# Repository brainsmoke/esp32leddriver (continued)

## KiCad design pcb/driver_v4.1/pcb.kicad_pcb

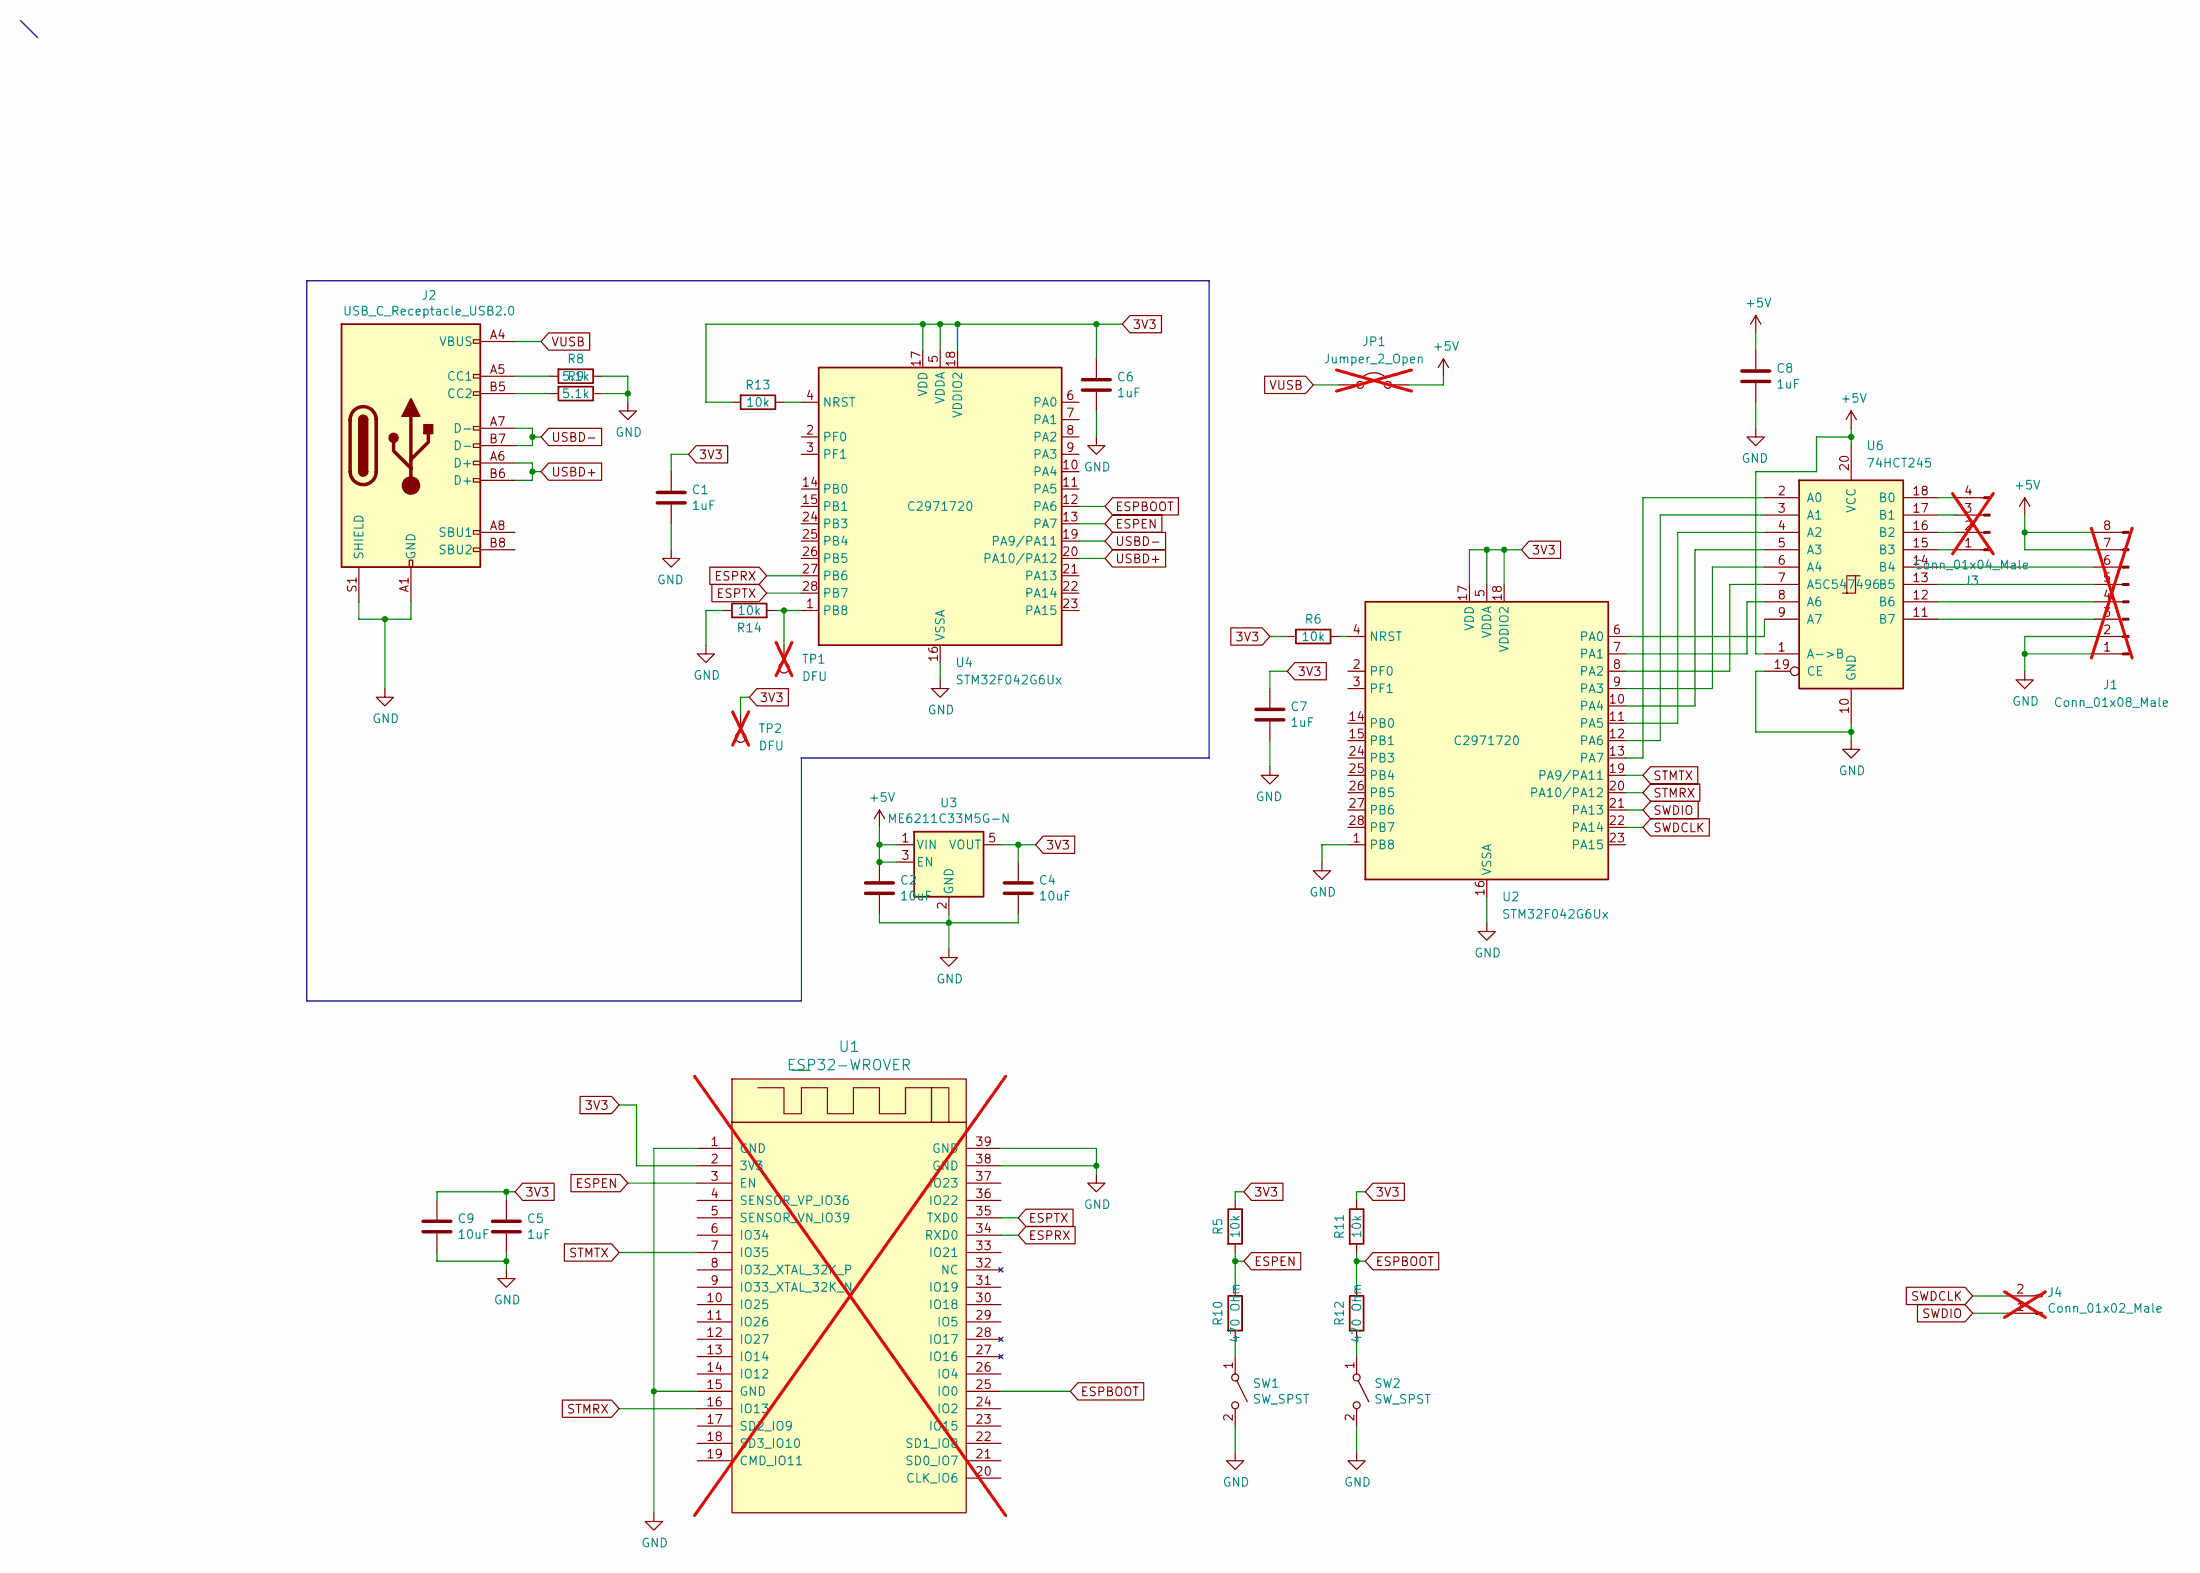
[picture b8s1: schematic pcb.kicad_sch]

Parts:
C1, C5, C6, C7, C8: 1uF; C_0402_1005Metric; LCSC C52923
C2, C4, C9: 10uF; C_0603_1608Metric; LCSC C19702
J1: Conn_01x08_Male; PinHeader_1x08_P2.54mm_Vertical; not fitted
J2: USB_C_Receptacle_USB2.0; USB_C_Receptacle_HRO_TYPE-C-31-M-12; LCSC C165948
J3: Conn_01x04_Male; PinHeader_1x04_P2.54mm_Vertical; not fitted
J4: Conn_01x02_Male; PinHeader_1x02_P2.54mm_Vertical; not fitted
JP1: Jumper_2_Open; R_0805_2012Metric; not fitted
R5, R6, R11, R13, R14: 10k; R_0402_1005Metric; LCSC C25744
R8, R9: 5.1k; R_0402_1005Metric; LCSC C25905
R10, R12: 470 Ohm; R_0402_1005Metric; LCSC C25117
SW1, SW2: SW_SPST; SW_Push_1P1T_NO_CK_KMR2; LCSC C318893
TP1, TP2: DFU; TestPoint_Pad_D1.0mm; not fitted
U1: ESP32-WROVER; XCVR_ESP32-WROVER; not fitted
U2, U4: STM32F042G6Ux; QFN-28_4x4mm_P0.5mm; LCSC C2971720
U3: ME6211C33M5G-N; SOT-23-5; LCSC C82942
U6: 74HCT245; DHVQFN-20-1EP_2.5x4.5mm_P0.5mm_EP1x3mm; LCSC C547496

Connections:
3V3: C1.1, C4.1, C5.1, C6.1, C7.1, C9.1, R5.1, R6.2, R11.1, R13.2, TP2.1, U1.2 (3V3), U2.5 (VDDA), U2.17 (VDD), U2.18 (VDDIO2), U3.5 (VOUT), U4.5 (VDDA), U4.17 (VDD), U4.18 (VDDIO2)
+5V: C2.1, C8.1, J1.7, J1.8, JP1.2 (B), U3.1 (VIN), U3.3 (EN), U6.1 (A->B), U6.20 (VCC)
ESPBOOT: R11.2, R12.1, U1.25 (IO0), U4.12 (PA6)
ESPEN: R5.2, R10.1, U1.3 (EN), U4.13 (PA7)
ESPRX: U1.34 (RXD0), U4.27 (PB6)
ESPTX: U1.35 (TXD0), U4.28 (PB7)
GND: C1.2, C2.2, C4.2, C5.2, C6.2, C7.2, C8.2, C9.2, J1.1, J1.2, J2.A1 (GND), J2.A12 (GND), J2.B1 (GND), J2.B12 (GND), J2.S1 (SHIELD), R8.1, R9.1, R14.1, SW1.2 (B), SW2.2 (B), U1.1 (GND), U1.15 (GND), U1.38 (GND), U1.39 (GND), U2.1 (PB8), U2.16 (VSSA), U3.2 (GND), U4.16 (VSSA), U6.10 (GND), U6.19 (CE)
unnamed: J1.3, U6.11 (B7)
unnamed: J1.4, U6.12 (B6)
unnamed: J1.5, U6.13 (B5)
unnamed: J1.6, U6.14 (B4)
unnamed: J2.A5 (CC1), R8.2
unnamed: J2.B5 (CC2), R9.2
unnamed: J3.1, U6.15 (B3)
unnamed: J3.2, U6.16 (B2)
unnamed: J3.3, U6.17 (B1)
unnamed: J3.4, U6.18 (B0)
unnamed: R10.2, SW1.1 (A)
unnamed: R12.2, SW2.1 (A)
unnamed: R6.1, U2.4 (NRST)
unnamed: U2.6 (PA0), U6.9 (A7)
unnamed: U2.7 (PA1), U6.8 (A6)
unnamed: U2.8 (PA2), U6.7 (A5)
unnamed: U2.9 (PA3), U6.6 (A4)
unnamed: U2.10 (PA4), U6.5 (A3)
unnamed: U2.11 (PA5), U6.4 (A2)
unnamed: U2.12 (PA6), U6.3 (A1)
unnamed: U2.13 (PA7), U6.2 (A0)
unnamed: R13.1, U4.4 (NRST)
unnamed: R14.2, TP1.1, U4.1 (PB8)
STMRX: U1.16 (IO13), U2.20 (PA10/PA12)
STMTX: U1.7 (IO35), U2.19 (PA9/PA11)
SWDCLK: J4.2, U2.22 (PA14)
SWDIO: J4.1, U2.21 (PA13)
USBD+: J2.A6 (D+), J2.B6 (D+), U4.20 (PA10/PA12)
USBD-: J2.A7 (D-), J2.B7 (D-), U4.19 (PA9/PA11)
VUSB: J2.A4 (VBUS), J2.A9 (VBUS), J2.B4 (VBUS), J2.B9 (VBUS), JP1.1 (A)

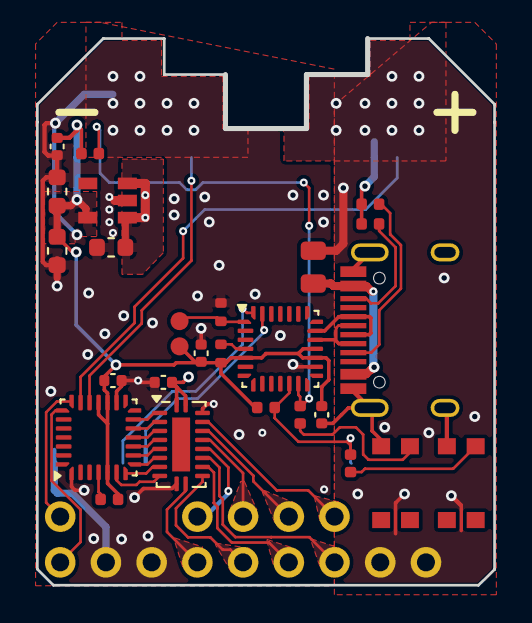
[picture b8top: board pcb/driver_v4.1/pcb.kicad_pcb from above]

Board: 4 copper layers, 25.4 x 30.4 mm, 31 parts (1 on the bottom side), 37 nets.

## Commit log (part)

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2021-04-17 esp_http_server bindings for micropython
2021-04-17 add README.md for esphttpd
2021-04-17 spaces -> tabs
2021-04-17 fix header code
2021-04-23 fast gamma table calculation
2021-04-23 http misc encodeing/decoding
2021-04-23 interface change
2021-04-23 config scripts
2021-04-23 gamma table test
2021-04-23 fix long lines
2021-04-23 fix long lines fix :-X
2021-04-24 preliminary gamma/brightness sliders
2021-04-27 add bufcpy
2021-04-27 revamp webinterface backend
2021-04-28 fix stack UAF in case a request object escapes the handler
2021-04-28 automatically detach from screen for uploads
2021-04-28 screen attach directly
2021-04-28 use flexbox layout
2021-04-29 static spots & chromatic abberation settings
2021-04-30 add Request.get_host()
2021-04-30 add csrf checks
2021-04-30 fix session cookie retrieval
2021-05-01 use ecdsa
2021-05-01 ampy get wrapper
2021-05-01 add socket info calls to request, use https only csrf cookies
2021-05-02 relay ball binaries
2021-05-03 use LED remapping
2021-05-03 happier colors for lorenz animation
2021-05-03 add possibility for api key
2021-05-03 add dirdiff script
2021-05-03 add LED groupings
2021-05-03 oops
2021-05-04 inject some initial random into lorenz
2021-05-04 load circuits file
2021-05-04 add classic electron model animation
2021-05-04 add 'faces' animation
2021-05-05 fix hsi
2021-05-05 tweak faces 'animation'
2021-05-05 combine shader with other animations
2021-05-05 include calculation scripts
2021-05-05 fix json so that it parses in cpython
2021-05-05 remap version of v1 ball
2021-05-05 add firmware binary, install & build instructions (wip)
2021-05-05 move test file out of fs directory
2021-05-05 remove pre-remap v1 model, since the remap model works
2021-05-06 do stuff while waiting for wifi
2021-05-06 remove broken script
2021-05-06 typos
2021-05-07 delayer decorator
2021-05-07 clean up
2021-05-07 use locks to properly protect brightness changes
2021-05-10 fix typo in old style makefile
2021-05-12 Use a jitter hiding framebuffer queue
2021-05-12 updated firmware
2021-05-13 add bytearray_max function
2021-05-13 misc debug code
2021-05-13 add hard reset script
2021-05-13 add firmware binary
2021-05-13 fix hang on exit
2021-05-14 move ColorDrift class to C module for speed
2021-05-14 fix exception handling in player
2021-05-14 add latest firmware image
2021-05-14 Edit README with build instructions
2021-11-16 add 16 bit uart frame pusher
2021-11-16 improve brightness adjustment perception
2021-11-16 improve boot time, wifi setup
2021-11-16 add test pattern
2021-11-16 add alu ball model
2021-11-20 remove unused native functions
2021-11-21 simplefy/decompose native framebuffer functions
2021-11-21 48bit colors
2021-11-23 add 16 bit led driver rom
2021-11-26 fix glitch
2021-12-07 Fix readme with help from sebastius
2021-12-29 add relay chip code
2021-12-29 use python3 instead of python to run dirdiff
2022-02-21 add button press code for config mode
2022-02-22 failsafe access point
2022-02-22 fix access point race condition for failsafe mode
2022-03-13 more tests
2022-03-24 use external xtal for tester
2022-03-25 clear leds between tests
2022-03-29 add guide pcb
2022-05-15 add failsafe label/code generator
2022-05-15 kill screen for dirdiff.sh
2022-05-15 fix failsafe for when there is no configured network yet
2022-07-17 allow open wifi networks
2022-07-17 add option to select open network in the failsafe menu
2022-07-19 show network info for last connection in failsafe mode
2022-09-03 new driver versions
2022-11-27 add build scripts
2022-11-29 port/rebase onto recent micropython
2022-11-29 revert back to MP_OBJ_NEW_QSTR
    use of MP_ROM_QSTR not needed to fix compile.
    debug mistake due to stale compilation intermediates
2022-11-29 use ThreadSafeFlag.clear()
2022-11-29 add new firmware binary
2022-12-01 fix stack overflow in webserver thread while parsing json
2022-12-01 add firmware.bin
2022-12-03 fix typo in documentation
2023-02-28 add relay binaries
2023-02-28 add tester binaries
2023-02-28 add softpwm binaries
2023-04-04 add uartball binary
2023-04-15 add readme
2023-04-23 add low-voltage-reset erratum workaround
2023-04-24 sync led driver
2023-04-24 remove cache file
2023-04-29 sync softpwmpdk
2023-08-30 add timing tester
2023-09-01 5 strip code
2023-09-01 make 5 strip code pass emulator test
2023-09-01 rename bitbang16_5strip.*
2023-09-01 rename bitbang routine
2023-09-01 clean up unneeded files
2023-09-01 remove unused file
2023-09-01 rename main16 -> dither16
2023-09-01 renae main -> dither8
2023-09-01 rename edgeball16 -> strip4
2023-09-01 rm binaries
2023-09-01 fix filename in Makefile test
2023-09-01 add support for pulse width configuration
2023-09-01 alternative driver pcb
2023-09-02 force pulse width parameters to be ints
2023-09-03 improve readme
2023-09-05 ignore cache file
2023-09-05 add chiral tiling model
2023-10-04 it compiles
2023-10-04 add uart2 dma code to util.c
2023-10-04 add penta pcb
2023-10-16 add raw frame pushing for testing purposes
2023-10-16 test/fix mapping
2023-11-01 add dma based ws2812 code
2023-12-02 new ws2812 driver implementation
2023-12-02 add missing linker script
2023-12-02 add support for led order configuration
2023-12-21 add pin number labels
2023-12-23 tweak settings for different spheres
2023-12-23 add earth animation for original ball
2023-12-23 modify upload script so that it'll only upload the right model files
2023-12-23 add inside wobble
2023-12-24 make fps configurable
2023-12-24 remove oD sphere specific animations from default main.py
2023-12-24 move animation selection to conf dir
2023-12-24 move wavetable generation to separate file
2023-12-24 add other waveforms
2023-12-24 add speed slider for multiwave
2023-12-24 add chromatic abberation slider to multiwave
2023-12-24 ani/orbit: don't light up inside
2023-12-24 remove waveform selection from spiral animation
2023-12-24 add shadowplay animation
2023-12-24 add shadowwalk
2023-12-25 remove unused animations from configs
2023-12-25 inverse sawtooth
2023-12-25 add groups .json for odsphere
2023-12-25 prettier topo
2023-12-26 fix topo max phase
2023-12-26 improve fire at all speeds
2023-12-27 add snake animation
2023-12-27 explicitly close file
2023-12-27 drop static 'animations' for polyhedrone
2023-12-27 make multiwave use leds.groups['leds']
2023-12-27 make fire animation the default for minipoly
2023-12-28 improve random colors, make fire CA more configurable
2023-12-28 parameterise fire
2023-12-28 start snake with bright initial color
2023-12-28 change orbit of one of the light sourrces on alienplanet
2023-12-28 alienplanet: fix intensity (oops)
2023-12-28 alienplanet: fix color selection
2023-12-29 update config example to reflect changes
2023-12-29 chiral tiling: use correct path for model selection
2023-12-29 tidy up flash script
2023-12-29 use export for envvar in readme
2023-12-29 add bmp flash instructions to m02812 readme
2023-12-29 missing $
2023-12-29 integrate aluball specific code
2024-01-07 don't drop into failsafe mode if there is no failsafe config
2024-01-10 add wiring documentation & case svg
2024-01-13 reorganize files
2024-01-13 add missing configurations
2024-01-13 README: Add comment for alternative shapes
2024-01-13 README: add images
2024-01-13 typo
2024-01-13 Add more pictures
2024-01-13 fix cornercase where max_colors > n_leds
2024-01-14 fix req.get_path() wrong length calculation
    luckily not exploitable due to limited control
2024-01-15 use external stylesheet
2024-01-15 rename group
2024-01-18 add wiring diagrams
2024-01-18 fix topo button ordering
2024-01-18 add webdir to upload script
2024-02-04 add random walk to chiral tiling
2024-02-04 ordered pcb
2024-02-04 use better variable name
2024-02-04 allow for per-model default settings
2024-02-04 increase default max speed
2024-02-04 add snake animation to greatcircles
2024-02-09 add monochrome support to uartpixel
2024-03-06 firmware for slim v2 driver
2024-05-18 fix dma base implementation
2024-05-18 fix interrupt priority issue / test performance
2024-05-18 increase recv buffer
2024-05-23 probably fix the dithering
2024-06-11 move common code to ./common/
2024-06-11 fix enabling output pin
2024-06-11 make dma transfer width configurable (untested)
2024-06-11 move firmwares to separate directories
2024-06-11 stm32: add gitignore
2024-06-11 remove unused,unfinished code
2024-06-11 fix make clean
2024-06-11 fix make test
2024-06-11 rename dma implementation to ws2812_dma16
2024-06-14 [common] add some defines
2024-06-14 [stm32] add uartrelay [untested]
2024-06-14 fix O_MASK define
2024-06-14 [stm32] [untested] add uartdemux, gpio_dma.[ch]
2024-06-16 speed optimisations
2024-06-16 win some cycles
2024-06-19 test & fix bugs in uartdemux
2024-06-19 spaces -> tab
2024-06-19 update protocol fsm to ignore possible future commands
2024-06-20 fix 8 bit width ws2812 DMA code
2024-06-23 increase receive buffer size
2024-06-23 pull unused pins high
2024-06-24 invert bits
2024-06-25 make padding explicit
2024-06-25 improve temporal dithering for huge chiral sphere
2024-06-25 restore correct initial output value
2024-06-25 simple best effort corrupt frame discard
2024-07-02 invert bits of initial out frame
2024-07-02 fix spelling mistake
2025-01-03 fix led position calculation
2025-01-04 add led computation code for chiral spheres to repo
2025-03-23 add binary flash script leaving filesystem intact
2025-03-23 add relay firmware for new PCB version (pin PA0 used instead of pin PA4
2025-03-24 add image of latest sphere
2025-04-23 update programming script
2025-05-08 use stm32 as usbserial
2025-05-08 minor tweak
2025-05-08 convert v3.2 to kicad 9
2025-06-10 IKEA OBEGRÄNSAD code, untested
2025-06-11 use correct LED map
2025-06-12 fix glitch at startup
2025-06-14 reduce upload speed for reliability
2025-06-14 update sym lib table for old pcb
2025-06-14 add next/previous push button option
2025-06-15 add initial obegraensad configuration
2025-06-16 add obegraensad readme
2025-06-16 readme
2025-06-16 grammar
2025-06-16 clarification
2025-06-17 add animation
2025-06-17 adjust gamma in movie
2025-06-17 smooth out pwm waveforms a bit
2025-06-20 update movie
2025-06-20 update docs
2025-06-20 alt text
2025-06-20 add pictures
2025-06-20 move delay_ger to common/m0delay.S
2025-06-20 add hexdump matrix code
2025-06-20 fix link
2025-06-20 add driver wiring image
2025-06-20 add level shifter comment
2025-06-20 add updated version of v4
2025-06-22 split out io part from obegraensad driver to help porting
2025-06-22 get rid of io_poll in main loop, makes no sense anyway
2025-06-23 README: link to alternative firmware
2025-06-24 improve readme a bit
2025-06-24 add ESP32 software description
2025-07-01 fix wraparound bug related to utime.ticks_ms()
2025-07-02 slight tweak of VCC zone
2025-07-04 fall back to failsafe mode if network configuration fails
2025-07-04 fix synax error
2025-07-04 play normal animations during failsafe mode
2025-07-04 remove unused variable
2025-07-05 didn't test the most common code-path Yesterday :,-)
2025-07-05 fix configuration animation adjust for new waveform size
2025-07-05 scan for networks
2025-07-05 report IP address on configuration
2025-07-05 fix crash when main network not configured
2025-07-05 clean up main.py
2025-07-06 remove superfluous statement
2025-07-06 capitalize hallway
2025-07-07 pretty-print network info
2025-07-07 configure internal pull-up to boot pin
2025-07-18 add WIFI-mecard QR codes to failsafe labels
2025-07-22 ticks_diff() is signed
2025-07-22 button bug
2025-07-23 add jump-to-configuration button to admin mode
2025-07-23 add exit to disable bootpin script
2025-07-23 make fewer assumptions about thread scheduling when dropping to failsafe mode
2025-09-06 actively drive unused pin to prevent noise
    just a precaution
2025-09-14 add scripts using black magic probe
2025-09-14 update elf binaries
2025-09-14 ignore pycache
2025-09-14 add faisafe network display scripts
2025-09-14 add compact driver PCB
2025-09-14 port pcbs to kicad 9
2025-09-14 remove obsolete netlist files
2025-09-14 get rid of rescued symbols
2025-09-14 remove unused cache libs
2025-09-14 ignore drc reports
2025-09-14 cleanup
2025-09-14 add gerbers for minimal driver board
2025-09-14 ignore tmp build dir
2025-09-14 make ignore tmpdir absolute
2025-09-14 import new sheets from pcbnew
